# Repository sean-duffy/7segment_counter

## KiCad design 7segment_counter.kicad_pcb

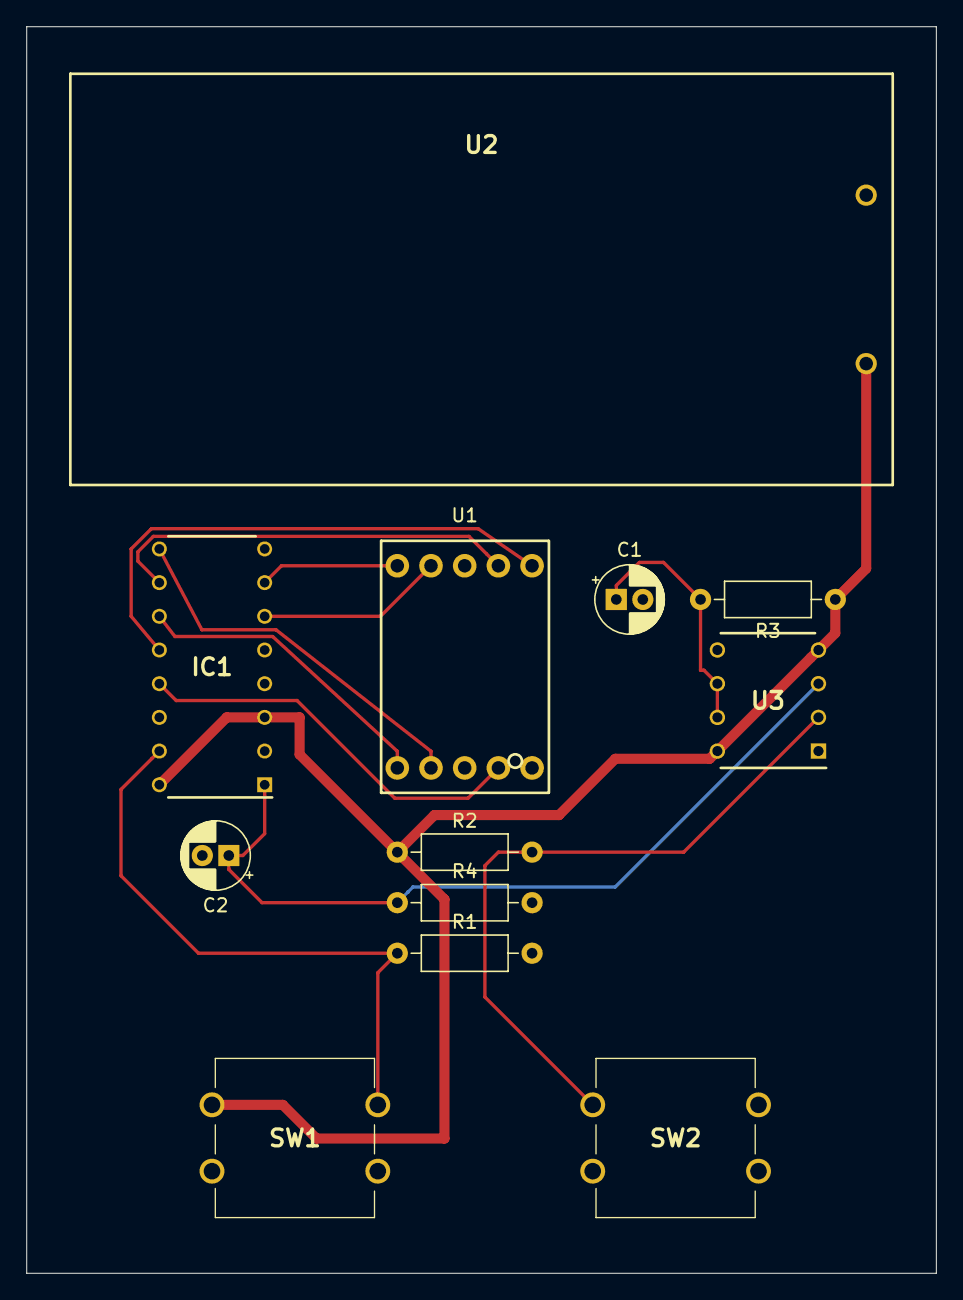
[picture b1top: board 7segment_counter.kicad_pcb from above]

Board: 2 copper layers, 68.6 x 94.0 mm, 12 parts (0 on the bottom side), 13 nets.

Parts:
C1: 1uF; CP_Radial_D5.0mm_P2.00mm
C2: 22uF; CP_Radial_D5.0mm_P2.00mm
IC1: CD4026BE; DIP794W53P254L1930H508Q16N
R1, R2, R3: 10k; R_Axial_DIN0207_L6.3mm_D2.5mm_P10.16mm_Horizontal
R4: 100k; R_Axial_DIN0207_L6.3mm_D2.5mm_P10.16mm_Horizontal
SW1: SW_Reset; MJTP1212
SW2: SW_Count; MJTP1212
U1: 5611AH
U2: 2462; COMF_AA_Holder
U3: ICM7555; DIP762W56P254L959H533Q8N

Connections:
GND: C1.2, C2.2, IC1.2, IC1.8, R1.2, R4.2, SW2.2, U1.3, U1.8, U2.2, U3.1
unnamed: C1.1, R3.2, U3.6, U3.7
unnamed: C2.1, IC1.1, R4.1, U3.3
unnamed: IC1.6, U1.2
unnamed: IC1.7, U1.1
unnamed: IC1.9, U1.7
unnamed: IC1.10, U1.4
unnamed: IC1.11, U1.6
unnamed: IC1.12, U1.5
unnamed: IC1.13, U1.9
unnamed: IC1.15, R1.1, SW1.2
unnamed: R2.2, SW2.1, U3.2
VCC: IC1.3, IC1.16, R2.1, R3.1, SW1.1, U2.1, U3.4, U3.8

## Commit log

2020-12-24 Working with one digit
2020-12-27 Add second digit
2020-12-27 Complete PCB connections
2020-12-27 Minor changes
2020-12-27 Change symbol library to use relative path
2020-12-27 Copy parts into project and fix library references
2020-12-27 Remove single digit pcb
2021-01-16 Fix switches
2021-01-16 Fix battery holder dimensions and digit positions
